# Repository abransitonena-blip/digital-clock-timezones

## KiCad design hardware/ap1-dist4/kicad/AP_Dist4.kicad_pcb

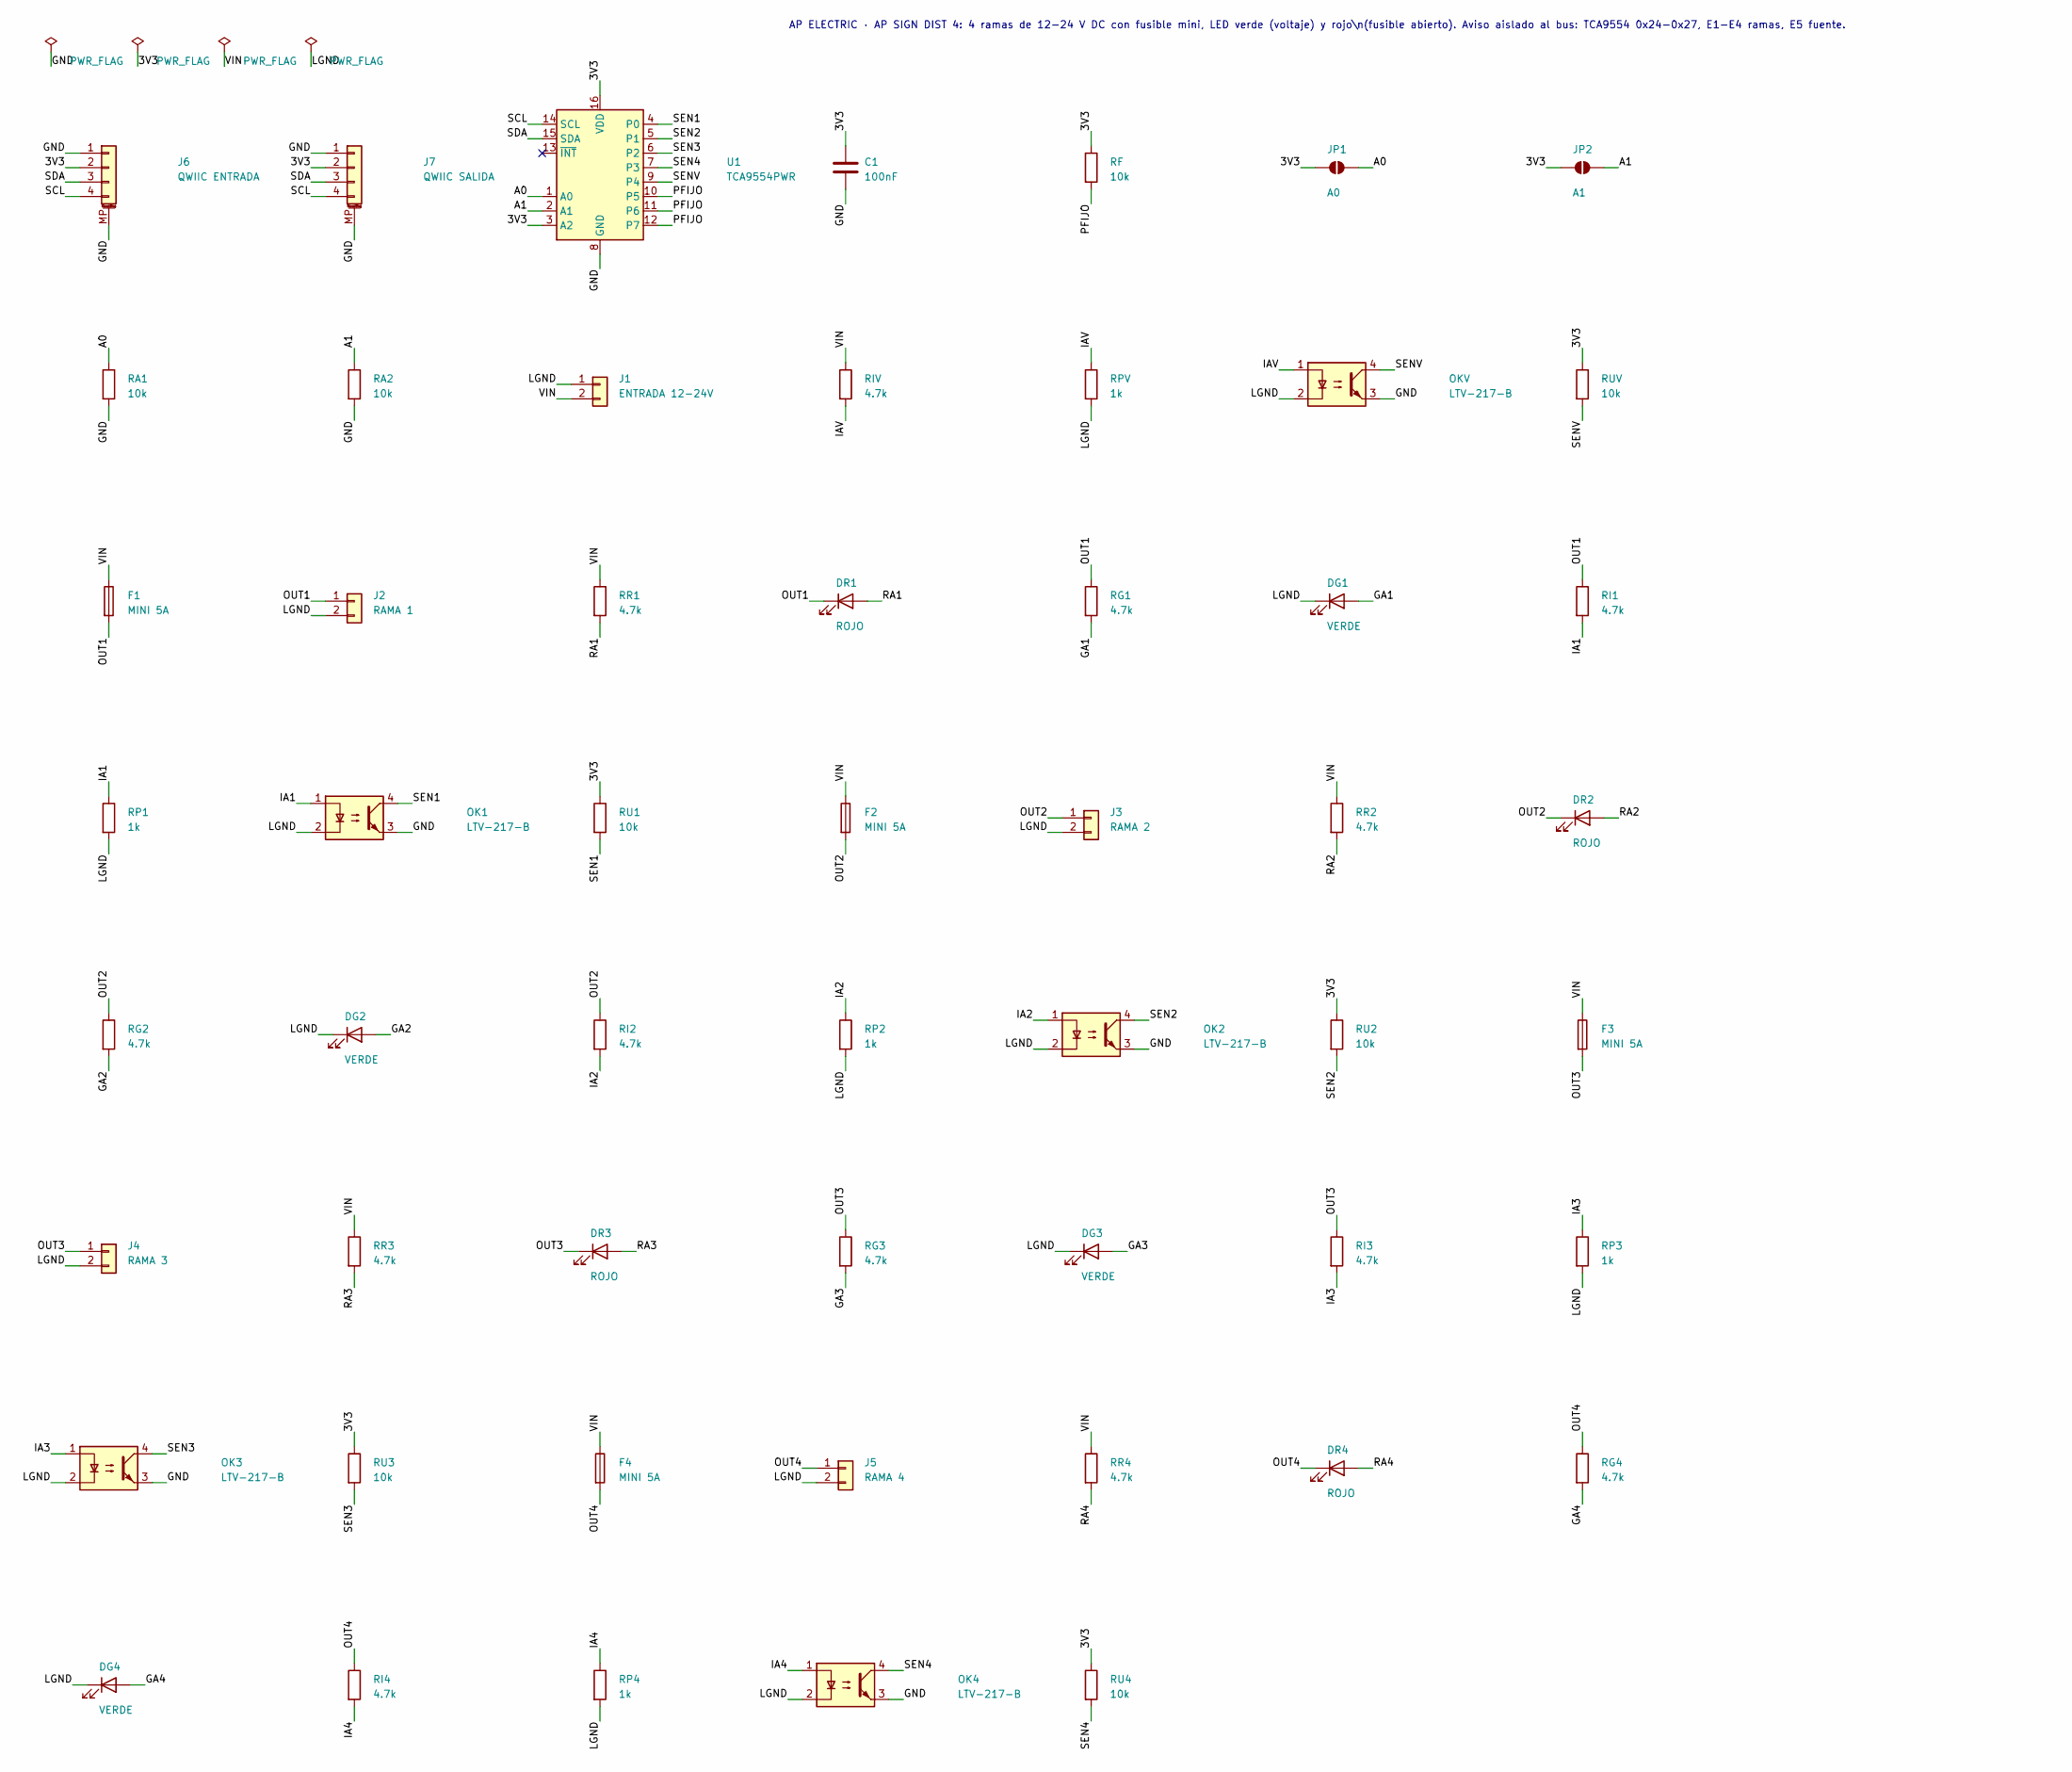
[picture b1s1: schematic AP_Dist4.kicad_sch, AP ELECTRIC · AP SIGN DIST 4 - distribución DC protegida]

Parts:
C1: 100nF; C_0603_1608Metric
DG1, DG2, DG3, DG4: VERDE; LED_0603_1608Metric
DR1, DR2, DR3, DR4: ROJO; LED_0603_1608Metric
F1, F2, F3, F4: MINI 5A; Fuseholder_Blade_Mini_Keystone_3568
J1: ENTRADA 12-24V; AMASS_XT60PW-M_1x02_P7.20mm_Horizontal
J2: RAMA 1; JST_VH_B2P-VH_1x02_P3.96mm_Vertical
J3: RAMA 2; JST_VH_B2P-VH_1x02_P3.96mm_Vertical
J4: RAMA 3; JST_VH_B2P-VH_1x02_P3.96mm_Vertical
J5: RAMA 4; JST_VH_B2P-VH_1x02_P3.96mm_Vertical
J6: QWIIC ENTRADA; JST_SH_SM04B-SRSS-TB_1x04-1MP_P1.00mm_Horizontal
J7: QWIIC SALIDA; JST_SH_SM04B-SRSS-TB_1x04-1MP_P1.00mm_Horizontal
JP1: A0; SolderJumper-2_P1.3mm_Open_RoundedPad1.0x1.5mm
JP2: A1; SolderJumper-2_P1.3mm_Open_RoundedPad1.0x1.5mm
OK1, OK2, OK3, OK4: LTV-217-B; SOP-4_4.4x2.6mm_P1.27mm
OKV: LTV-217-B; SOP-4_4.4x2.6mm_P1.27mm
RA1, RA2: 10k; R_0603_1608Metric
RF: 10k; R_0603_1608Metric
RG1, RG2, RG3, RG4: 4.7k; R_1206_3216Metric
RI1, RI2, RI3, RI4: 4.7k; R_1206_3216Metric
RIV: 4.7k; R_1206_3216Metric
RP1, RP2, RP3, RP4: 1k; R_0603_1608Metric
RPV: 1k; R_0603_1608Metric
RR1, RR2, RR3, RR4: 4.7k; R_1206_3216Metric
RU1, RU2, RU3, RU4: 10k; R_0603_1608Metric
RUV: 10k; R_0603_1608Metric
U1: TCA9554PWR; TSSOP-16_4.4x5mm_P0.65mm

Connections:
/3V3: C1.1, J6.2, J7.2, JP1.1 (A), JP2.1 (A), RF.1, RU1.1, RU2.1, RU3.1, RU4.1, RUV.1, U1.3 (A2), U1.16 (VDD)
/A0: JP1.2 (B), RA1.1, U1.1 (A0)
/A1: JP2.2 (B), RA2.1, U1.2 (A1)
/GA1: DG1.2 (A), RG1.2
/GA2: DG2.2 (A), RG2.2
/GA3: DG3.2 (A), RG3.2
/GA4: DG4.2 (A), RG4.2
/GND: C1.2, J6.1, J6.MP (MountPin), J7.1, J7.MP (MountPin), OK1.3, OK2.3, OK3.3, OK4.3, OKV.3, RA1.2, RA2.2, U1.8 (GND)
/IA1: OK1.1, RI1.2, RP1.1
/IA2: OK2.1, RI2.2, RP2.1
/IA3: OK3.1, RI3.2, RP3.1
/IA4: OK4.1, RI4.2, RP4.1
/IAV: OKV.1, RIV.2, RPV.1
/LGND: DG1.1 (K), DG2.1 (K), DG3.1 (K), DG4.1 (K), J1.1, J2.2, J3.2, J4.2, J5.2, OK1.2, OK2.2, OK3.2, OK4.2, OKV.2, RP1.2, RP2.2, RP3.2, RP4.2, RPV.2
/OUT1: DR1.1 (K), F1.2, J2.1, RG1.1, RI1.1
/OUT2: DR2.1 (K), F2.2, J3.1, RG2.1, RI2.1
/OUT3: DR3.1 (K), F3.2, J4.1, RG3.1, RI3.1
/OUT4: DR4.1 (K), F4.2, J5.1, RG4.1, RI4.1
/PFIJO: RF.2, U1.10 (P5), U1.11 (P6), U1.12 (P7)
/RA1: DR1.2 (A), RR1.2
/RA2: DR2.2 (A), RR2.2
/RA3: DR3.2 (A), RR3.2
/RA4: DR4.2 (A), RR4.2
/SCL: J6.4, J7.4, U1.14 (SCL)
/SDA: J6.3, J7.3, U1.15 (SDA)
/SEN1: OK1.4, RU1.2, U1.4 (P0)
/SEN2: OK2.4, RU2.2, U1.5 (P1)
/SEN3: OK3.4, RU3.2, U1.6 (P2)
/SEN4: OK4.4, RU4.2, U1.7 (P3)
/SENV: OKV.4, RUV.2, U1.9 (P4)
/VIN: F1.1, F2.1, F3.1, F4.1, J1.2, RIV.1, RR1.1, RR2.1, RR3.1, RR4.1

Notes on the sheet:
AP ELECTRIC · AP SIGN DIST 4: 4 ramas de 12-24 V DC con fusible mini, LED verde (voltaje) y rojo\n(fusible abierto). Aviso aislado al bus: TCA9554 0x24-0x27, E1-E4 ramas, E5 fuente.

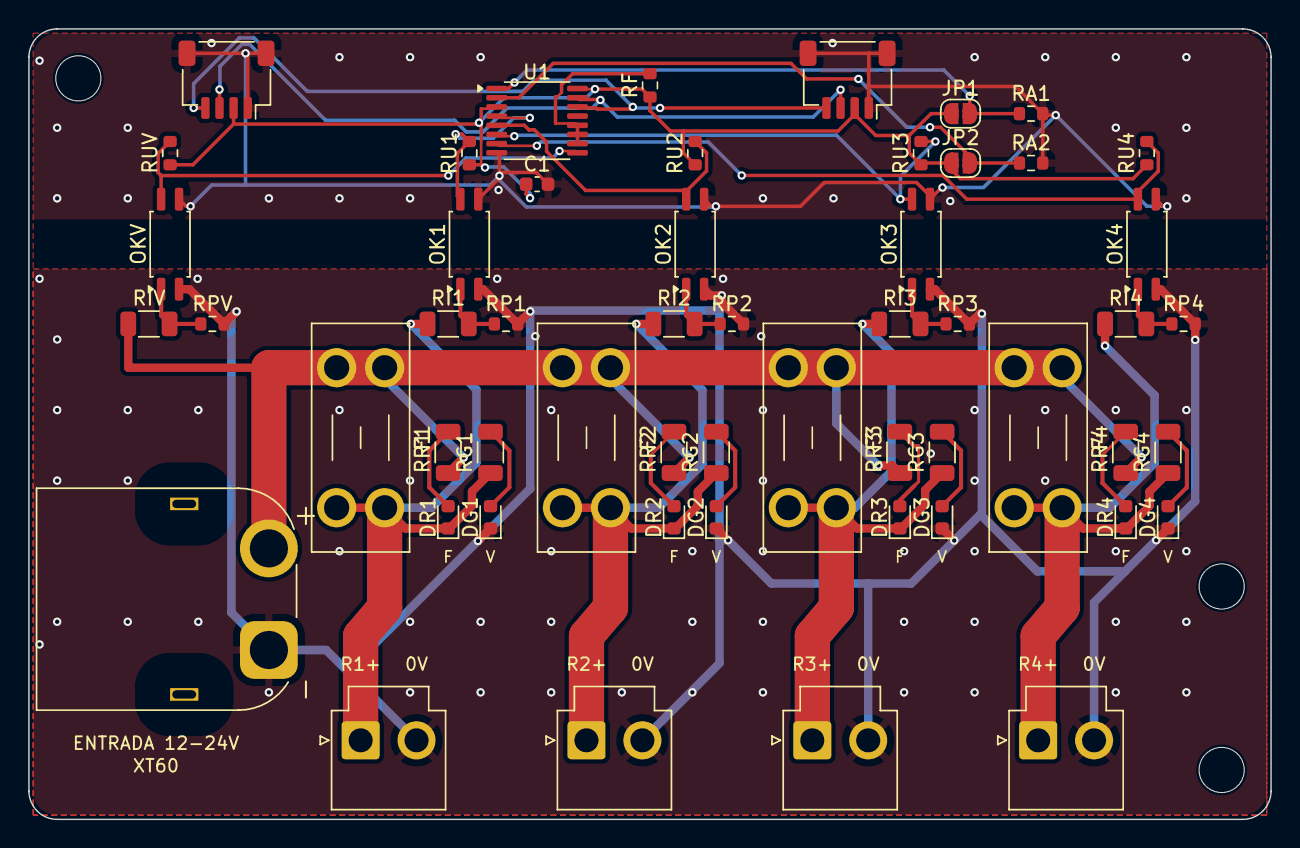
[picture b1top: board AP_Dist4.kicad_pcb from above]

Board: 2 copper layers, 88.0 x 56.0 mm, 57 parts (0 on the bottom side), 31 nets.

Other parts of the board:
H1, H2, H3: MountingHole_3.2mm_M3

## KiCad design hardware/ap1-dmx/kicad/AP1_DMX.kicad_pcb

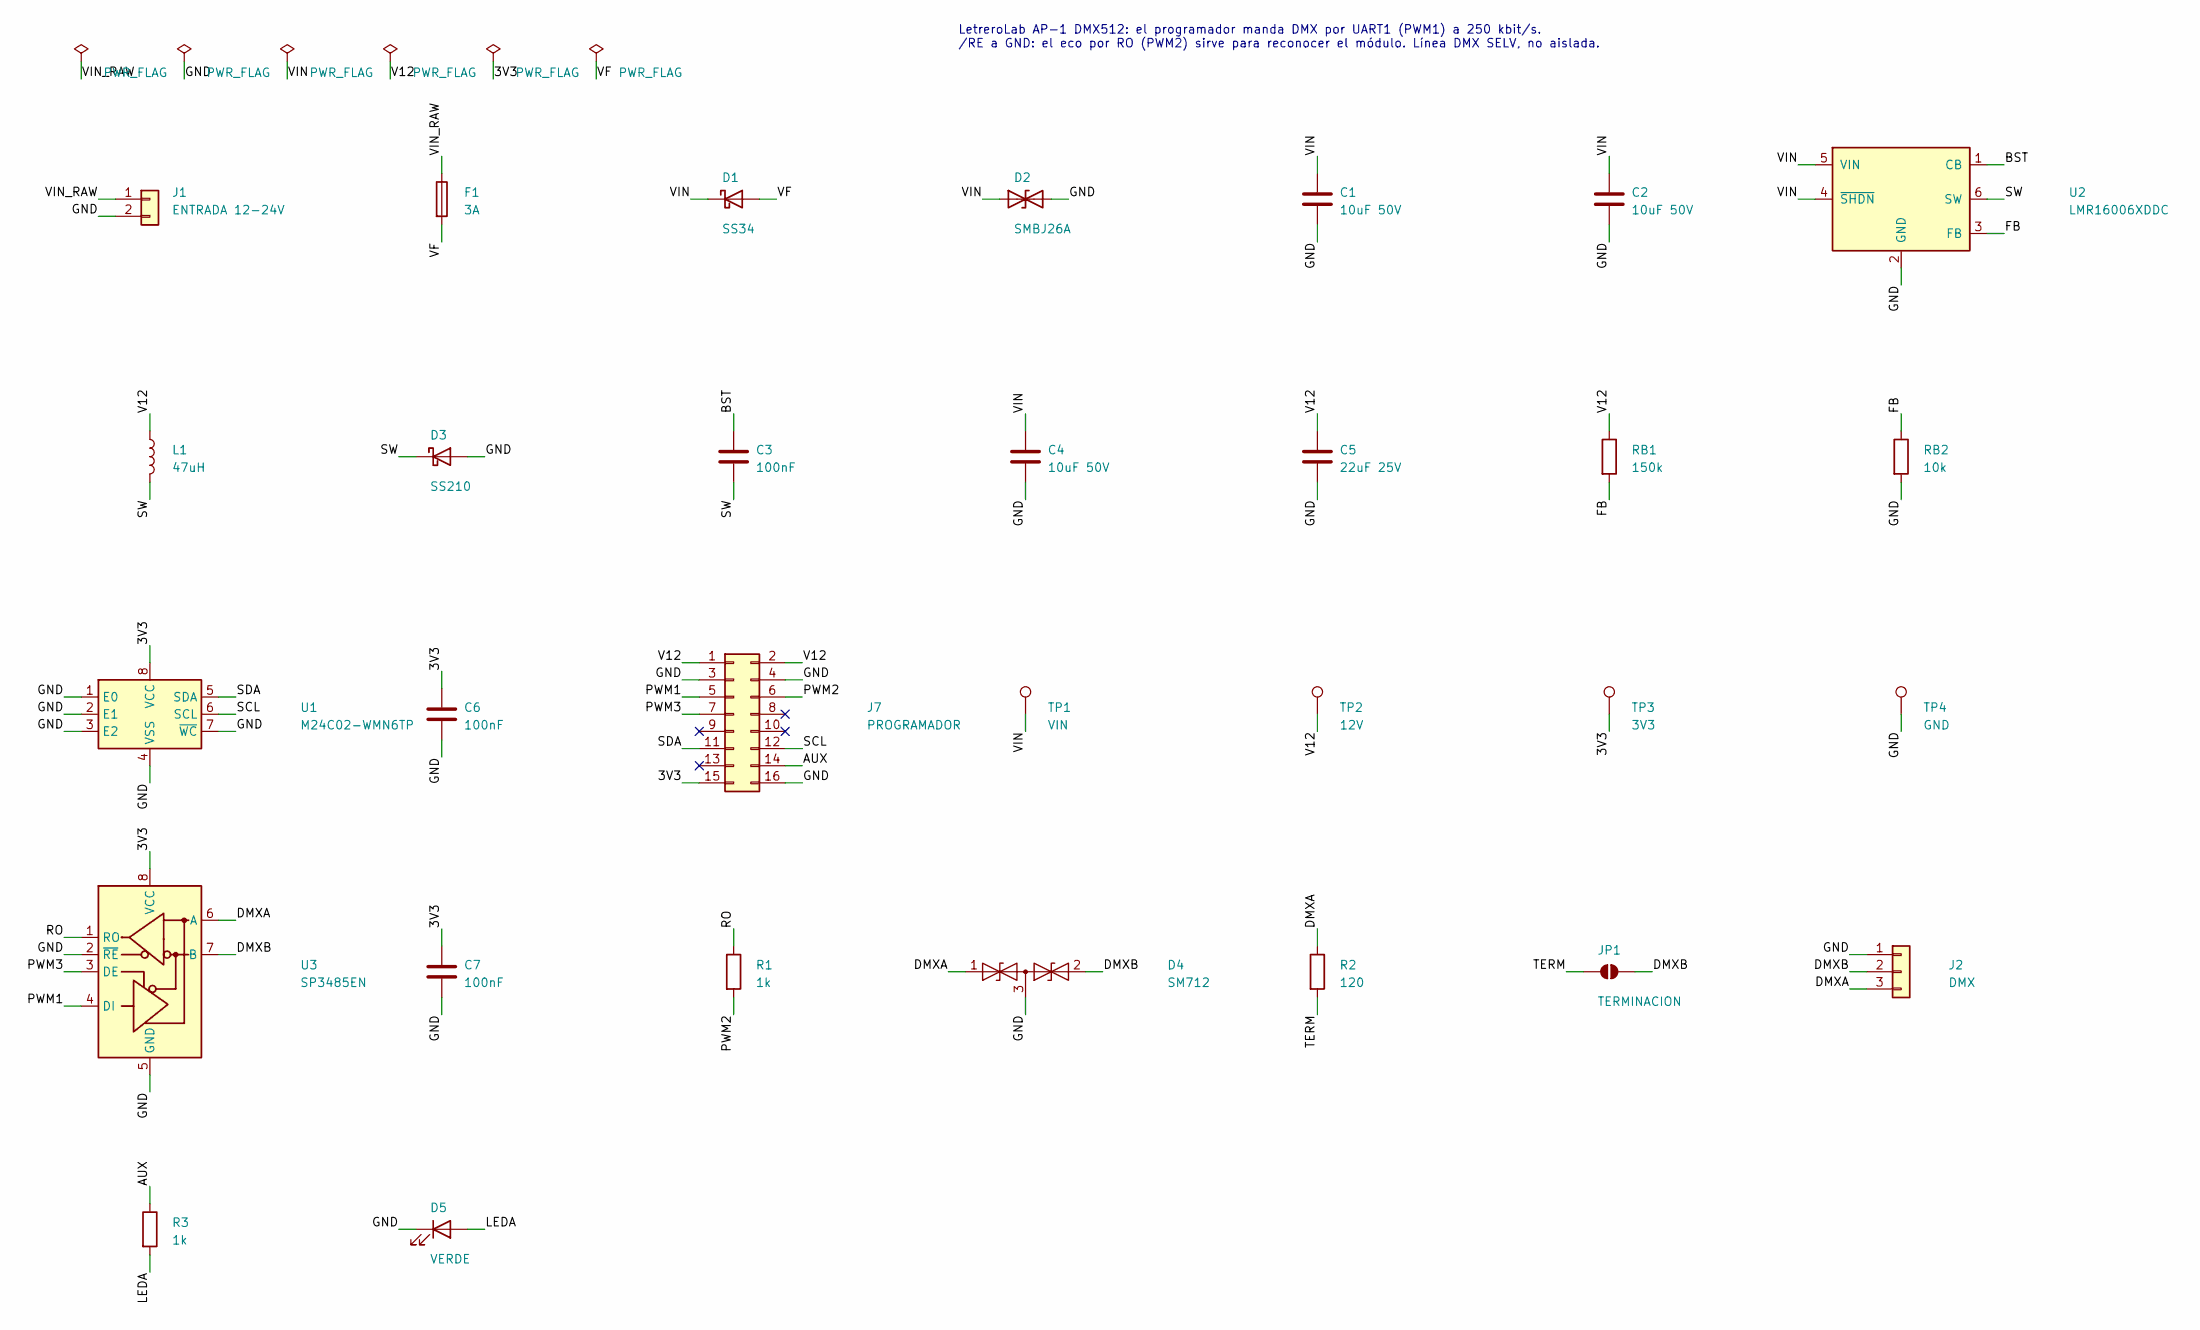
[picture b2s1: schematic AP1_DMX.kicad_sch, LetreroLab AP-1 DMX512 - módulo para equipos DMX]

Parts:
C1, C2, C4: 10uF 50V; C_1206_3216Metric
C3, C6, C7: 100nF; C_0603_1608Metric
C5: 22uF 25V; C_1206_3216Metric
D1: SS34; D_SMA
D2: SMBJ26A; D_SMB
D3: SS210; D_SMA
D4: SM712; SOT-23
D5: VERDE; LED_0603_1608Metric
F1: 3A; Fuse_1206_3216Metric
J1: ENTRADA 12-24V; JST_VH_B2P-VH_1x02_P3.96mm_Vertical
J2: DMX; JST_XH_B3B-XH-A_1x03_P2.50mm_Vertical
J7: PROGRAMADOR; PinSocket_2x08_P2.54mm_Vertical
JP1: TERMINACION; SolderJumper-2_P1.3mm_Open_RoundedPad1.0x1.5mm
L1: 47uH; L_Changjiang_FNR4030S
R1, R3: 1k; R_0603_1608Metric
R2: 120; R_1206_3216Metric
RB1: 150k; R_0603_1608Metric
RB2: 10k; R_0603_1608Metric
TP1: VIN; TestPoint_Pad_D1.5mm
TP2: 12V; TestPoint_Pad_D1.5mm
TP3: 3V3; TestPoint_Pad_D1.5mm
TP4: GND; TestPoint_Pad_D1.5mm
U1: M24C02-WMN6TP; SOIC-8_3.9x4.9mm_P1.27mm
U2: LMR16006XDDC; SOT-23-6
U3: SP3485EN; SOIC-8_3.9x4.9mm_P1.27mm

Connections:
/3V3: C6.1, C7.1, J7.15, TP3.1, U1.8 (VCC), U3.8 (VCC)
/AUX: J7.14, R3.1
/BST: C3.1, U2.1 (CB)
/DMXA: D4.1 (A1), J2.3, R2.1, U3.6 (A)
/DMXB: D4.2 (A2), J2.2, JP1.2 (B), U3.7 (B)
/FB: RB1.2, RB2.1, U2.3 (FB)
/GND: C1.2, C2.2, C4.2, C5.2, C6.2, C7.2, D2.2 (A2), D3.2 (A), D4.3 (common), D5.1 (K), J1.2, J2.1, J7.3, J7.4, J7.16, RB2.2, TP4.1, U1.1 (E0), U1.2 (E1), U1.3 (E2), U1.4 (VSS), U1.7 (~WC), U2.2 (GND), U3.2 (~RE), U3.5 (GND)
/LEDA: D5.2 (A), R3.2
/PWM1: J7.5, U3.4 (DI)
/PWM2: J7.6, R1.2
/PWM3: J7.7, U3.3 (DE)
/RO: R1.1, U3.1 (RO)
/SCL: J7.12, U1.6 (SCL)
/SDA: J7.11, U1.5 (SDA)
/SW: C3.2, D3.1 (K), L1.2, U2.6 (SW)
/TERM: JP1.1 (A), R2.2
/V12: C5.1, J7.1, J7.2, L1.1, RB1.1, TP2.1
/VF: D1.2 (A), F1.2
/VIN: C1.1, C2.1, C4.1, D1.1 (K), D2.1 (A1), TP1.1, U2.4 (~SHDN), U2.5 (VIN)
/VIN_RAW: F1.1, J1.1

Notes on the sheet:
LetreroLab AP-1 DMX512: el programador manda DMX por UART1 (PWM1) a 250 kbit/s. /RE a GND: el eco por RO (PWM2) sirve para reconocer el módulo. Línea DMX SELV, no aislada.

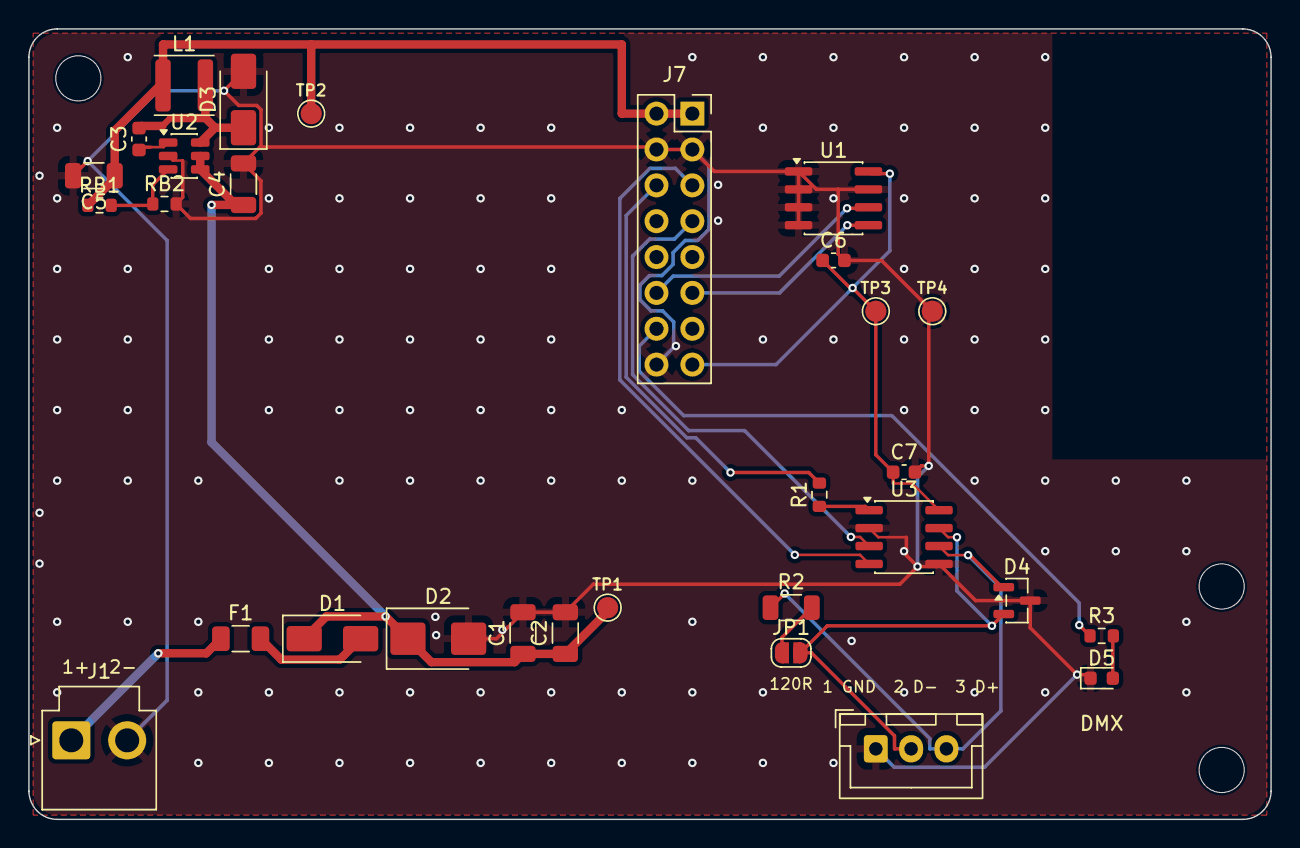
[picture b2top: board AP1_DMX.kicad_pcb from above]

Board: 2 copper layers, 88.0 x 56.0 mm, 33 parts (0 on the bottom side), 20 nets.

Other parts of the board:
H1, H2, H3: MountingHole_3.2mm_M3

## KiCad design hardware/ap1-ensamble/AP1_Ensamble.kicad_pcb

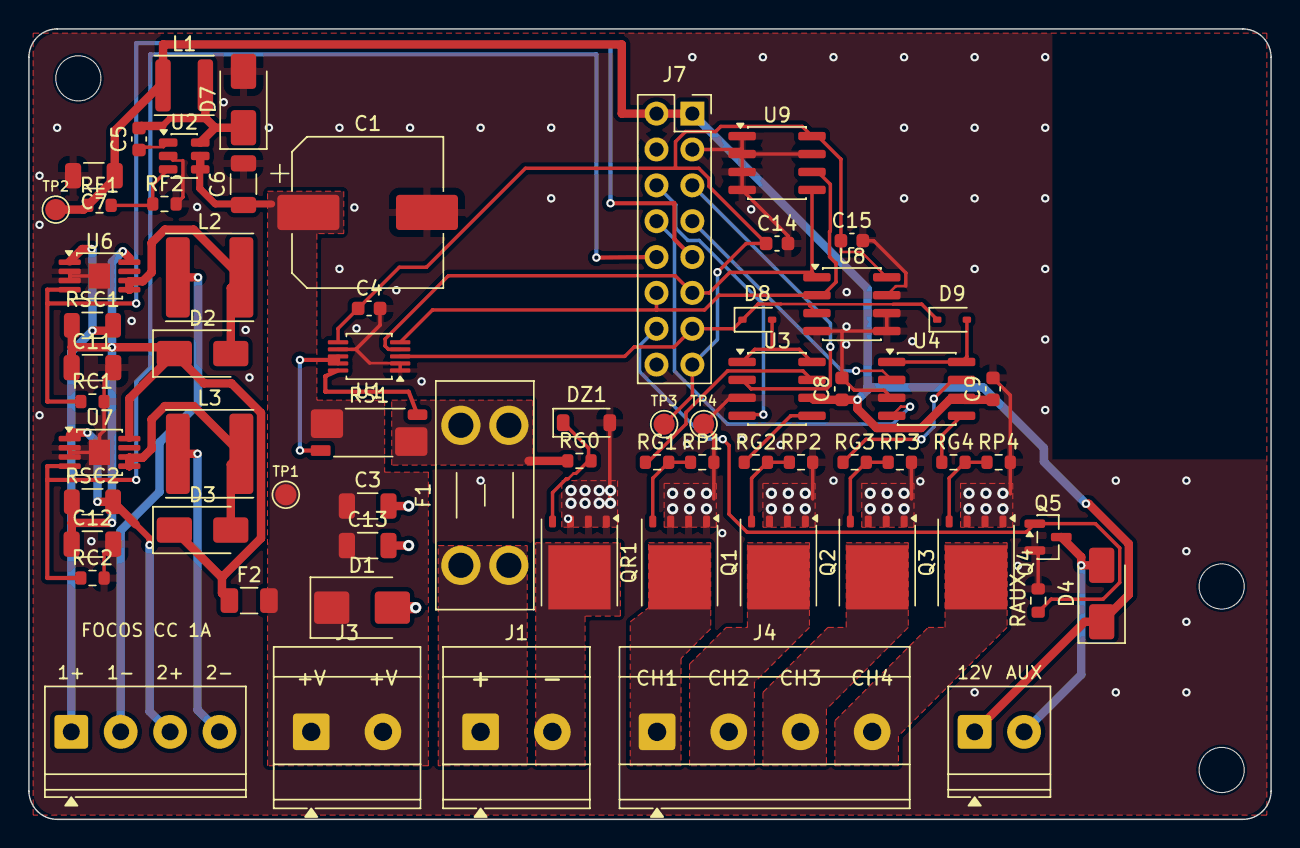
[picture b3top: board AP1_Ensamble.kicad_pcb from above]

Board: 4 copper layers, 88.0 x 56.0 mm, 71 parts (0 on the bottom side), 45 nets.

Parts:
C1: 330uF 50V; CP_Elec_10x10.5
C3, C6, C13: 10uF 50V; C_1206_3216Metric
C4, C5, C14, C15: 100nF; C_0603_1608Metric
C7: 22uF 25V; C_1206_3216Metric
C8, C9: 1uF 25V; C_0603_1608Metric
C11, C12: 4.7uF 50V; C_1206_3216Metric
D1: SMBJ26A; D_SMB
D2, D3, D4: SS34; D_SMA
D7: SS210; D_SMA
D8, D9: 1N4148WS; D_SOD-323
DZ1: MMSZ5242B 12V; D_SOD-123
F1: MINI 20A; Fuseholder_Blade_Mini_Keystone_3568
F2: 3A; Fuse_1206_3216Metric
H1, H2, H3: MountingHole_3.2mm_M3
J1: ENTRADA 12-24V; TerminalBlock_Phoenix_MKDS-3-2-5.08_1x02_P5.08mm_Horizontal
J3: +V SALIDA; TerminalBlock_Phoenix_MKDS-3-2-5.08_1x02_P5.08mm_Horizontal
J4: CANALES; TerminalBlock_Phoenix_MKDS-3-4-5.08_1x04_P5.08mm_Horizontal
J5: FOCOS CC; TerminalBlock_Phoenix_PT-1,5-4-3.5-H_1x04_P3.50mm_Horizontal
J6: AUX 12V; TerminalBlock_Phoenix_PT-1,5-2-3.5-H_1x02_P3.50mm_Horizontal
J7: PROGRAMADOR; PinSocket_2x08_P2.54mm_Vertical
L1: 47uH; L_Changjiang_FNR4030S
L2, L3: 47uH; L_Changjiang_FNR6045S
PROG: (no value)
Q1, Q2, Q3, Q4: BSC028N06LS3; TDSON-8-1
Q5: AO3400A; SOT-23
QR1: BSC016N06NS; TDSON-8-1
RAUX: 10k; R_0603_1608Metric
RC1, RC2: 2.2k; R_0603_1608Metric
RF1: 150k; R_0603_1608Metric
RF2: 10k; R_0603_1608Metric
RG0: 10k; R_0603_1608Metric
RG1, RG2, RG3, RG4: 4.7; R_0603_1608Metric
RP1, RP2, RP3, RP4: 10k; R_0603_1608Metric
RS1: 1mR 2512 Kelvin; R_Shunt_Vishay_WSK2512_6332Metric_T1.19mm
RSC1, RSC2: 0R1; R_1206_3216Metric
TP1: VIN; TestPoint_Pad_D1.5mm
TP2: 12V; TestPoint_Pad_D1.5mm
TP3: 3V3; TestPoint_Pad_D1.5mm
TP4: GND; TestPoint_Pad_D1.5mm
U1: INA238; VSSOP-10_3x3mm_P0.5mm
U2: LMR16006XDDC; SOT-23-6
U3, U4: UCC27524D; SOIC-8_3.9x4.9mm_P1.27mm
U6, U7: AL8860MP; MSOP-8-1EP_3x3mm_P0.65mm_EP1.5x1.8mm
U8: TMP1075D; SOIC-8_3.9x4.9mm_P1.27mm
U9: M24C02-WMN6TP; SOIC-8_3.9x4.9mm_P1.27mm

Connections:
/3V3: C4.1, C14.1, C15.1, J7.15, TP3.1, U1.6, U8.8, U9.8
/ALERT: D8.1, D9.1, J7.13, U1.3, U8.3
/AUX: J7.14, Q5.1, RAUX.1
/AUXD: D4.2, J6.2, Q5.3
/BST2: C5.1, U2.1
/CC1: J7.9, RC1.1, U6.4
/CC2: J7.10, RC2.1, U7.4
/CH1: J4.1, Q1.5
/CH2: J4.2, Q2.5
/CH3: J4.3, Q3.5
/CH4: J4.4, Q4.5
/EN12: D8.2, U3.1, U3.8
/EN34: D9.2, U4.1, U4.8
/FB2: RF1.2, RF2.1, U2.3
/G1: Q1.4, RG1.2, RP1.1
/G2: Q2.4, RG2.2, RP2.1
/G3: Q3.4, RG3.2, RP3.1
/G4: Q4.4, RG4.2, RP4.1
/GND: C1.2, C3.2, C4.2, C6.2, C7.2, C8.2, C9.2, C11.2, C12.2, C13.2, C14.2, C15.2, D1.2, D7.2, DZ1.2, J7.3, J7.4, J7.16, Q1.1, Q1.2, Q1.3, Q2.1, Q2.2, Q2.3, Q3.1, Q3.2, Q3.3, Q4.1, Q4.2, Q4.3, Q5.2, QR1.1, QR1.2, QR1.3, RAUX.2, RC1.2, RC2.2, RF2.2, RP1.2, RP2.2, RP3.2, RP4.2, TP4.1, U1.1, U1.2, U1.7, U2.2, U3.3, U4.3, U6.2, U6.3, U6.9, U7.2, U7.3, U7.9, U8.4, U8.5, U8.6, U8.7, U9.1, U9.2, U9.3, U9.4, U9.7
/GNDIN: J1.2, QR1.5
/GO1: RG1.1, U3.7
/GO2: RG2.1, U3.5
/GO3: RG3.1, U4.7
/GO4: RG4.1, U4.5
/GREV: DZ1.1, QR1.4, RG0.2
/ISN: RS1.2, U1.8, U1.9
/ISP: RS1.3, U1.10
/LEDA1: J5.1, RSC1.2, U6.1
/LEDA2: J5.3, RSC2.2, U7.1
/LEDK1: J5.2, L2.1
/LEDK2: J5.4, L3.1
/PWM1: J7.5, U3.2
/PWM2: J7.6, U3.4
/PWM3: J7.7, U4.2
/PWM4: J7.8, U4.4
/SCL: J7.12, U1.5, U8.2, U9.6
/SDA: J7.11, U1.4, U8.1, U9.5
/SW2: C5.2, D7.1, L1.2, U2.6
/SWC1: D2.2, L2.2, U6.5, U6.6
/SWC2: D3.2, L3.2, U7.5, U7.6
/V12: C7.1, C8.1, C9.1, D4.1, J6.1, J7.1, J7.2, L1.1, RF1.1, TP2.1, U3.6, U4.6
/VCC: C11.1, C12.1, D2.1, D3.1, F2.1, RSC1.1, RSC2.1, U6.8, U7.8
/VF: F1.2, RG0.1, RS1.4
/VIN: C1.1, C3.1, C6.1, C13.1, D1.1, F2.2, J3.1, J3.2, RS1.1, TP1.1, U2.4, U2.5
/VIN_RAW: F1.1, J1.1

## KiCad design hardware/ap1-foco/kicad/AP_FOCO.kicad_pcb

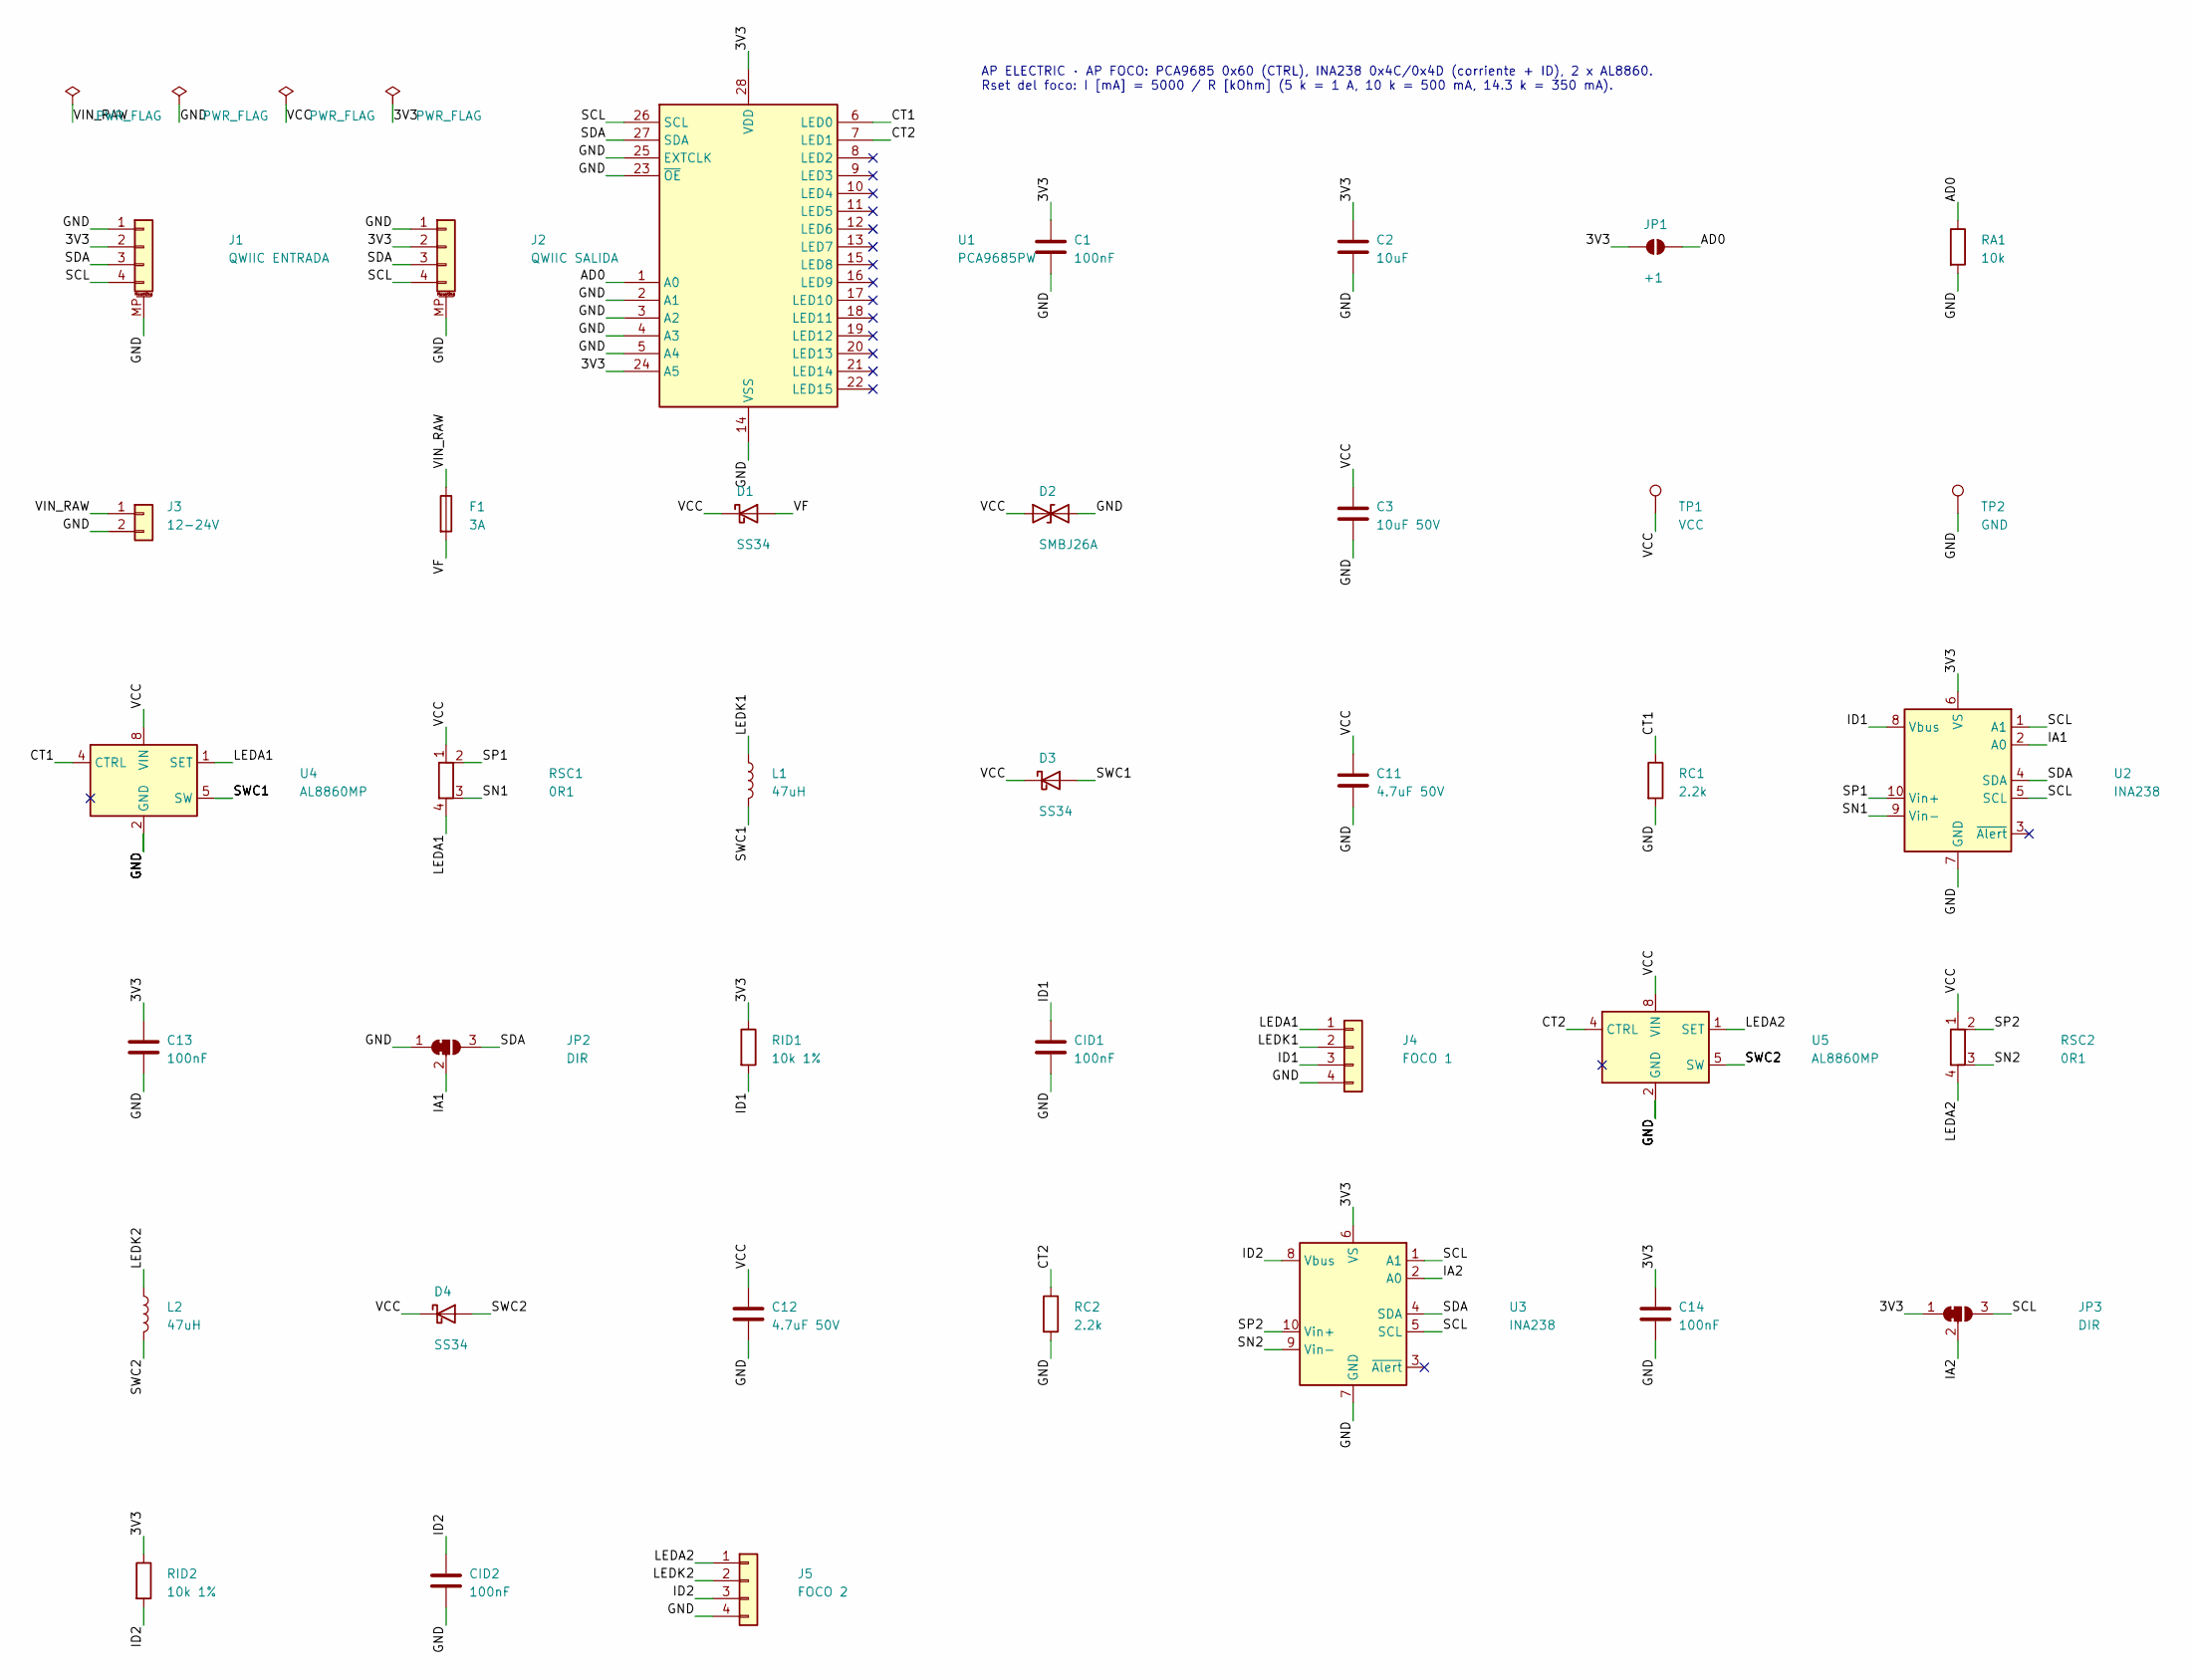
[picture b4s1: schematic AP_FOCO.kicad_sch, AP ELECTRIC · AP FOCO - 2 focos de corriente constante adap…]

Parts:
C1, C13, C14: 100nF; C_0603_1608Metric
C2: 10uF; C_0805_2012Metric
C3: 10uF 50V; C_1206_3216Metric
C11, C12: 4.7uF 50V; C_1206_3216Metric
CID1, CID2: 100nF; C_0603_1608Metric
D1, D3, D4: SS34; D_SMA
D2: SMBJ26A; D_SMB
F1: 3A; Fuse_1206_3216Metric
J1: QWIIC ENTRADA; JST_SH_SM04B-SRSS-TB_1x04-1MP_P1.00mm_Horizontal
J2: QWIIC SALIDA; JST_SH_SM04B-SRSS-TB_1x04-1MP_P1.00mm_Horizontal
J3: 12-24V; JST_VH_B2P-VH_1x02_P3.96mm_Vertical
J4: FOCO 1; JST_XH_B4B-XH-A_1x04_P2.50mm_Vertical
J5: FOCO 2; JST_XH_B4B-XH-A_1x04_P2.50mm_Vertical
JP1: +1; SolderJumper-2_P1.3mm_Open_RoundedPad1.0x1.5mm
JP2, JP3: DIR; SolderJumper-3_P1.3mm_Bridged12_RoundedPad1.0x1.5mm
L1, L2: 47uH; L_Changjiang_FNR6045S
RA1: 10k; R_0603_1608Metric
RC1, RC2: 2.2k; R_0603_1608Metric
RID1, RID2: 10k 1%; R_0603_1608Metric
RSC1, RSC2: 0R1; R_1206_Kelvin_NetTie
TP1: VCC; TestPoint_Pad_D1.5mm
TP2: GND; TestPoint_Pad_D1.5mm
U1: PCA9685PW; TSSOP-28_4.4x9.7mm_P0.65mm
U2, U3: INA238; VSSOP-10_3x3mm_P0.5mm
U4, U5: AL8860MP; MSOP-8-1EP_3x3mm_P0.65mm_EP1.5x1.8mm

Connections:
/3V3: C1.1, C2.1, C13.1, C14.1, J1.2, J2.2, JP1.1 (A), JP3.1 (A), RID1.1, RID2.1, U1.24 (A5), U1.28 (VDD), U2.6 (VS), U3.6 (VS)
/AD0: JP1.2 (B), RA1.1, U1.1 (A0)
/CT1: RC1.1, U1.6 (LED0), U4.4 (CTRL)
/CT2: RC2.1, U1.7 (LED1), U5.4 (CTRL)
/GND: C1.2, C2.2, C3.2, C11.2, C12.2, C13.2, C14.2, CID1.2, CID2.2, D2.2 (A2), J1.1, J1.MP (MountPin), J2.1, J2.MP (MountPin), J3.2, J4.4, J5.4, JP2.1 (A), RA1.2, RC1.2, RC2.2, TP2.1, U1.2 (A1), U1.3 (A2), U1.4 (A3), U1.5 (A4), U1.14 (VSS), U1.23 (~OE), U1.25 (EXTCLK), U2.7 (GND), U3.7 (GND), U4.2 (GND), U4.3 (GND), U4.9 (GND), U5.2 (GND), U5.3 (GND), U5.9 (GND)
/IA1: JP2.2 (C), U2.2 (A0)
/IA2: JP3.2 (C), U3.2 (A0)
/ID1: CID1.1, J4.3, RID1.2, U2.8 (Vbus)
/ID2: CID2.1, J5.3, RID2.2, U3.8 (Vbus)
/LEDA1: J4.1, RSC1.4, U4.1 (SET)
/LEDA2: J5.1, RSC2.4, U5.1 (SET)
/LEDK1: J4.2, L1.1
/LEDK2: J5.2, L2.1
/SCL: J1.4, J2.4, JP3.3 (B), U1.26 (SCL), U2.1 (A1), U2.5 (SCL), U3.1 (A1), U3.5 (SCL)
/SDA: J1.3, J2.3, JP2.3 (B), U1.27 (SDA), U2.4 (SDA), U3.4 (SDA)
/SN1: RSC1.3, U2.9 (Vin-)
/SN2: RSC2.3, U3.9 (Vin-)
/SP1: RSC1.2, U2.10 (Vin+)
/SP2: RSC2.2, U3.10 (Vin+)
/SWC1: D3.2 (A), L1.2, U4.5 (SW), U4.6 (SW)
/SWC2: D4.2 (A), L2.2, U5.5 (SW), U5.6 (SW)
/VCC: C3.1, C11.1, C12.1, D1.1 (K), D2.1 (A1), D3.1 (K), D4.1 (K), RSC1.1, RSC2.1, TP1.1, U4.8 (VIN), U5.8 (VIN)
/VF: D1.2 (A), F1.2
/VIN_RAW: F1.1, J3.1

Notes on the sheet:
AP ELECTRIC · AP FOCO: PCA9685 0x60 (CTRL), INA238 0x4C/0x4D (corriente + ID), 2 x AL8860. Rset del foco: I [mA] = 5000 / R [kOhm] (5 k = 1 A, 10 k = 500 mA, 14.3 k = 350 mA).

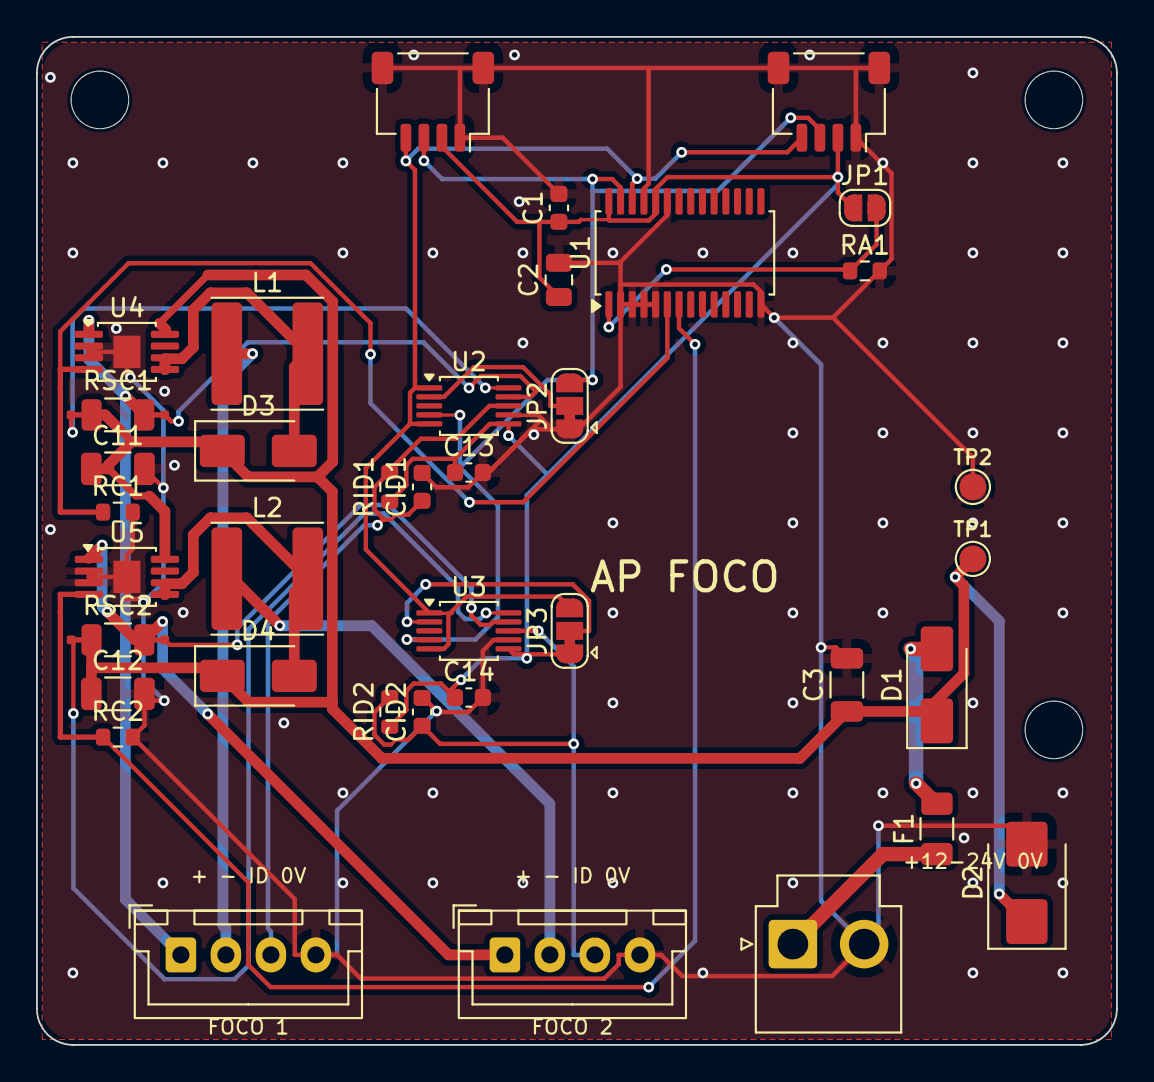
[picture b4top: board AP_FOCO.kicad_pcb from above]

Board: 2 copper layers, 60.0 x 56.0 mm, 41 parts (0 on the bottom side), 24 nets.

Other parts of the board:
H1, H2, H3: MountingHole_3.2mm_M3
